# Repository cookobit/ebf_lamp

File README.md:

# EBF Lamp Project

You came after the Electrical Blast Furnace (EBF) from GregTech modpacks, especially GTNH. 
This repository contains all production files to date, plus special 3D-print files you can print at home and assemble yourself.

## HOW TO PRINT THE EBF

1. Download the whole repository.
2. In the '3D_prints' folder, find files for 3D printing.
3. The STLs come in two options: the **lamp version**, or for the r**egular version** (empty inside), which is simpler.
4. The lamp version requires a custom PCB, a step-down voltage module, and a power inlet. Because of these custom components, a full reproduction of the lamp from this repo is not possible in its current state.

IMPORTANT: Current dimensions are 192x192x256 mm for the lamp, change the scale for regular version, since the lamp has mounting holes for M3 screws and other components.

## What's in this repository?
In short, the STLs I made so far, as well as some of the design files and software for ESP32 XIAO module. They are separated in two dedicated folders: firmware and hardware.
The firmware was used in the Arduino IDE for flashing the program there, and the hardware was designed in the KiCad, dedicated open-source PCB design software. 

## Plans for the future:

The repo won't have a complete support and maintained actively, because of the real life stuff.
* New PCB for electronics integration. It should integrate the power inlet and complete sensor and hardware integration.
* An optional buzzer for the EBF to make the "working" sounds.
* A humidifier on top, active while the EBF is "running".

## License
Hardware files are licensed under **CERN-OHL-P**; software is licensed under the **MIT License**. See the respective directories for full license text.

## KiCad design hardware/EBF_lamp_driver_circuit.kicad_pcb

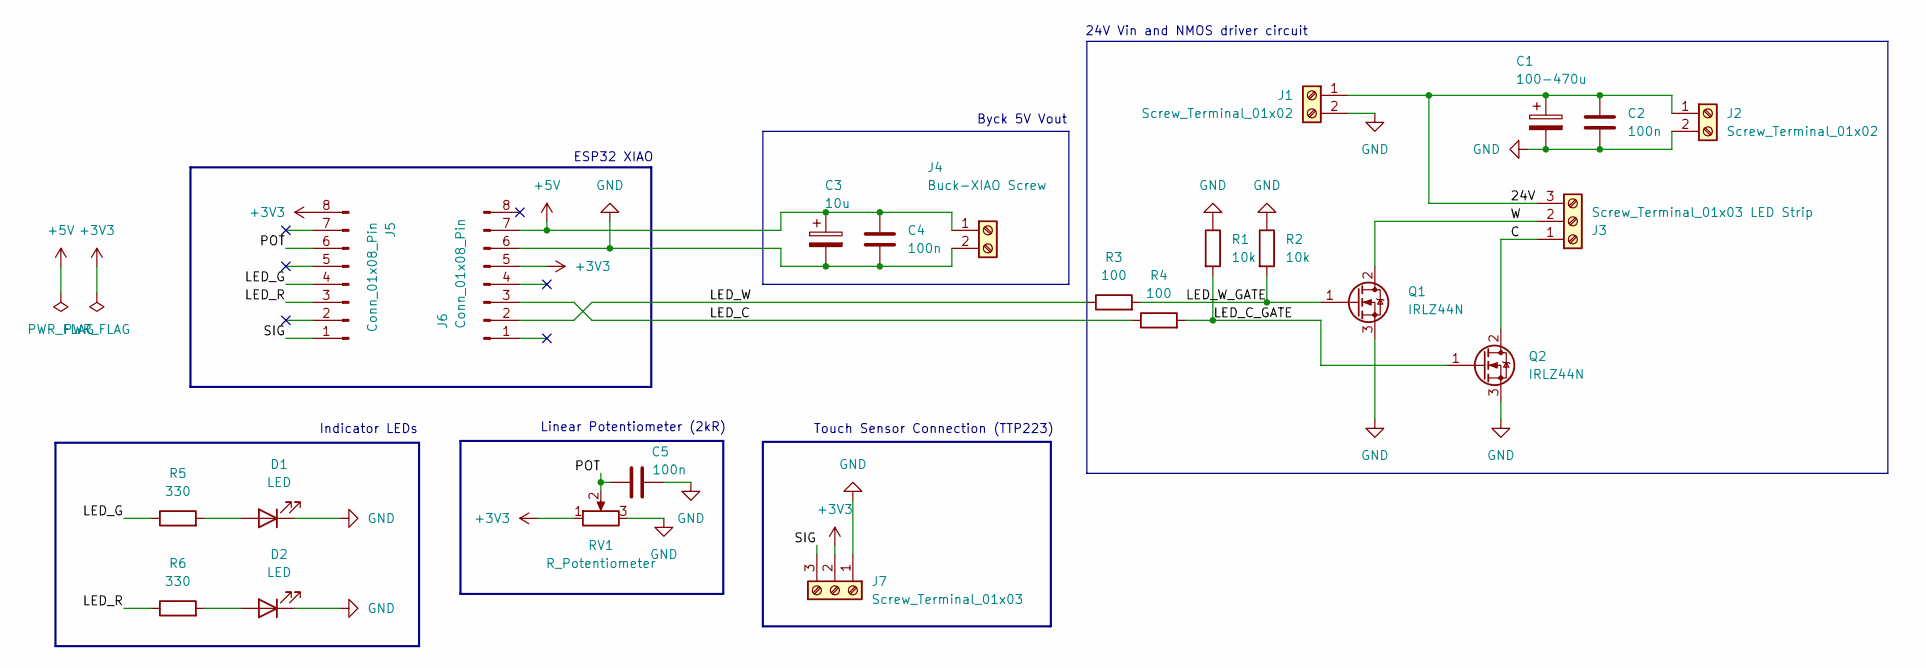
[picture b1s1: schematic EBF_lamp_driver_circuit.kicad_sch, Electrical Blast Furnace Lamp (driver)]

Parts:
C1: 100-470u; CP_Radial_D6.3mm_P2.50mm
C2, C4, C5: 100n; C_Disc_D3.0mm_W2.0mm_P2.50mm
C3: 10u; CP_Radial_D6.3mm_P2.50mm
D1, D2: LED; LED_D5.0mm
J1, J2: Screw_Terminal_01x02; TerminalBlock_RND_205-00045_1x02_P5.00mm_Horizontal
J3: Screw_Terminal_01x03 LED Strip; TerminalBlock_RND_205-00046_1x03_P5.00mm_Horizontal
J4: Buck-XIAO Screw; TerminalBlock_RND_205-00045_1x02_P5.00mm_Horizontal
J5, J6: Conn_01x08_Pin; PinSocket_1x08_P2.54mm_Vertical
J7: Screw_Terminal_01x03; TerminalBlock_RND_205-00046_1x03_P5.00mm_Horizontal
Q1, Q2: IRLZ44N; TO-220-3_Horizontal_TabDown
R1, R2: 10k; R_Axial_DIN0207_L6.3mm_D2.5mm_P10.16mm_Horizontal
R3, R4: 100; R_Axial_DIN0207_L6.3mm_D2.5mm_P10.16mm_Horizontal
R5, R6: 330; R_Axial_DIN0207_L6.3mm_D2.5mm_P10.16mm_Horizontal
RV1: R_Potentiometer; PinHeader_1x03_P2.54mm_Vertical

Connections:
+3V3: J5.8, J6.5, J7.2, RV1.1
+5V: C3.1, C4.1, J4.1, J6.7
/24V: C1.1, C2.1, J1.1, J2.1, J3.3
/C: J3.1, Q2.2 (D)
/LED_C: J6.3, R4.1
/LED_C_GATE: Q2.1 (G), R1.2, R4.2
/LED_G: J5.4, R5.1
/LED_R: J5.3, R6.1
/LED_W: J6.2, R3.1
/LED_W_GATE: Q1.1 (G), R2.2, R3.2
/POT: C5.1, J5.6, RV1.2
/SIG: J5.1, J7.3
/W: J3.2, Q1.2 (D)
GND: C1.2, C2.2, C3.2, C4.2, C5.2, D1.1 (K), D2.1 (K), J1.2, J2.2, J4.2, J6.6, J7.1, Q1.3 (S), Q2.3 (S), R1.1, R2.1, RV1.3
unnamed: D1.2 (A), R5.2
unnamed: D2.2 (A), R6.2

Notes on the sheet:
Touch Sensor Connection (TTP223)
Indicator LEDs
Linear Potentiometer (2kR)
Byck 5V Vout
ESP32 XIAO
24V Vin and NMOS driver circuit

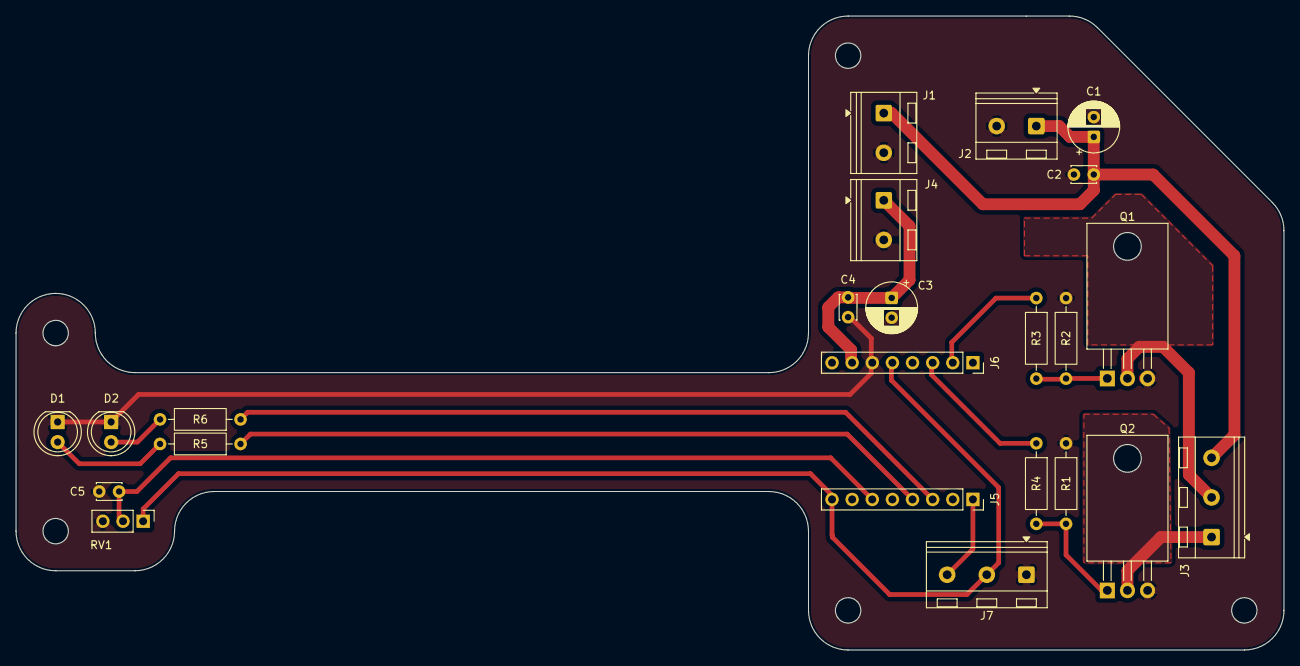
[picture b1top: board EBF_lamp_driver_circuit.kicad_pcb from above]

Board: 2 copper layers, 160.0 x 80.0 mm, 23 parts (0 on the bottom side), 16 nets.

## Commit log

2026-05-28 STL files
2026-05-28 folder
2026-05-28 Layout change
2026-05-28 Design Files
2026-05-28 organized
